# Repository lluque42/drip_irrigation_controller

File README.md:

# Drip irrigation controller

## Table of contents

- [Introduction](#introductions)
- [Building instructions](#building-instructions)
- [WiFi connectivity](#wifi-connectivity)
    - [UDP command messages](#udp-command-messages)
- [Directory tree](#directory-tree)
- [Hardware](#harware)

------

## Introduction

This drip irrigation controller was designed to control one relay for a water
electrovalve and a second relay for ornament lights. Both relays may be
configured for independent one-time-a-day activation to remain active during a
configurable time. The frequency in terms of days between activations is also
configurable. Any of the relays may be disabled which will stop their future scheduled activations.

A default configuration is applied at building time (edit files 'CMakeLists.txt',
'timers_default_data.cmake', and 'wlan_setup_data.cmake' to change it). The
controller configuration (get and set) and manual activation may be done
remotely through the wifi connection with simple UDP messages exchange.

This is the second controller I've built for my house plants.
The first was written in Python in a rush before going out on
a trip and worked perfectly. It had a dot matrix screen with
a setup menu through microswitches; a real-time clock module,
etc. But some years later it hangs a lot, outdoor installation
always takes its toll.

So I've decided to implement a new version that loses the screen
in favor of a WiFi connection for keep-alive signaling against
a server, configuration and commands.

This repository includes all the code and scripts to built the
program in a Raspberry Pi Pico (1) W board. The schematics for
the external hardware is also included.

**Luis Luque - 2025**

------

## Building instructions

REMEMBER: This code was made for and tested on a Pico W (first
family of the Raspberry Pi Pico series). Use at your own risk in
other platforms.

Clone repository from:

https://github.com/lluque42/drip_irrigation_controller.git

Two files are included to allow an easy customization:
* wlan_setup_data.cmake.template (rename to wlan_setup_data.cmake)
    * To enter the wifi SSID, password.
* timers_default_data.cmake
* To enter the time of the day, frequency and duration for
the relays activation.

Create a build directory and enter to it:

```bash
drip_irrigation_controller $ mkdir build
drip_irrigation_controller $ cd build
drip_irrigation_controller/build $
```

Once inside, execute cmake against the parent directory (where
the CMakeLists.txt is):

```bash
drip_irrigation_controller/build $ cmake ..
drip_irrigation_controller/build $
```

If no errors occurred, then a Makefile file should have been created
in the build directory. Execute it to build the binaries.

```bash
drip_irrigation_controller/build $ make
```

If everything ok, a number of binary files should've been produced,
among them a drip.elf or drip.uf2 ready to be loaded into the Pico W
board.

For building the tests tool, see the **Wifi connectivity** section.

If some error occur check the pre-requisites:
* The PICO_SDK_VARIABLE environment variable should exist and point to
the root of the pico-sdk directory.
* Is your board really a Pico W (first generation)?
* ?
TODO

------

## WiFi connectivity

The microcontroller can connect to a wireless network if the correct settings
were edited in the wlan_setup_data.cmake file (a template for this file is
provided, just write your settings and rename the file).

A static IPv4 address must be provided, as well as an UDP port (a high
non-common one to avoid issues). This is necessary for the controller to act as
a simple text UDP server. That is, it will open the UDP port listening for
incoming messages. A set of message formats define commands and responses
that may be sent to the controller and back.

The messages are plain-text ASCII, human readable, strings (without the NUL
termination), that is, a string sent as the payload of the UDP datagram.

A simple, dirty client (and a server) written to debug this program is included
as a git sub-module in:

```bash
drip_irrigation_controller/test/udp_tx_rx
```

Since it is a submodule it should be initialized from the
drip_irrigation_controller root directory by doing:

```bash
drip_irrigation_controller $ git submodule update --init --recursive
```

After that, both the client and server can be build with:

```bash
drip_irrigation_controller/test/udp_tx_rx $ make
```

Which places the binaries in the bin folder.

To use the client to communicate over the wifi with  the irrigation controller
(assuming the default values in the wlan_setup_data.cmake.template) just do:

```bash
.../test/udp_tx_rx/bin $ ./udp_client 192.168.1.69 1234
```

This will receive input from the stdin for the user to send text to the
controller.

The commands, their formats, and the expected replies are the following:

------

### UDP command messages

Below are the recognized command messages and their replies. The client
just need to write and read this as the payload of UDP messages to/from
the controller that acts as a server on the IP address and UDP port set
in the wlan_setup_data.cmake at build time.
* Set datetime:
	SET:DATETIME:YYYY:MM:DD:dotw:HH:mm:SS
		dotw: Day of the week 0-6. Sunday is 0.
* Set water timer parameters:
    SET:WATER:WTODHH:WTODmm:WTODSS:WEXD:DOW
        TOD: Time of day when activation should occur.
        EXD: Every X days, the X. Days between activations.
        DO:  Duration of activation.
* Set lights timer parameters:
    SET:LIGHTS:LTODHH:LTODmm:LTODSS:LEXD:DOL
        TOD: Time of day when activation should occur.
        EXD: Every X days, the X. Days between activations.
        DO:  Duration of activation.
* Get datetime:
    GET:DATETIME
        Response example: 2025:8:15:5:21:2:52
        (see SET:DATETIME format).
* Get water relay current configuration:
    GET:WATER
        Response example: 
            21:0:0:1:120:2025:8:15:5:21:0:0
        That is:
            Time of day: 21:0:0
            Every X days: 1
            Duration (sec): 120
            Next activation scheduled: 2025:8:16:6:21:0:0
            (see SET:DATETIME format).
* Get lights relay current configuration:
    GET:LIGHTS 
        Response example:
            21:0:0:1:10800:2025:8:15:5:21:0:0
        See GET:WATER format.
* Manual on lights.
	MANUALON:LIGHTS
* Manual off lights.
	MANUALOFF:LIGHTS
* Manual on water.
	MANUALON:WATER
* Manual off water.
	MANUALOFF:WATER
* Timed on lights (Force turn on for the duration configured).
	TIMEDON:LIGHTS
* Timed on irigation (Force turn on for the duration configured).
	TIMEDON:WATER

For non get commands, expect a response of "done" if it was correctly processed
or a custom human readable error message.

------

## Directory tree

TODO

    ./  
    ├── .gitignore				(to prevent undesired files to be stagged)
    ├── Doxyfile				(doxygen config file for doc generation)  
    ├── Makefile				(use 'make help' for instructions)  
    ├── README.md				(brief documentation)  
    ├── doc/					(documentation extracted from comments in .h)  
    │   ├── html/				(html documentation)  
    │   │   ├── ...  
    │   │   ├── index.html		(entry point for html documentation)  
    │   │   ├── ...  
    │   └── man/				(man pages documentation)  
    │       └── man3/  
    │           └── ...			(example of use: 'man -l ft_string.h.3')  
    ├── include/				(directory for public header files (.h))  
    │   ├── ...  
    │   └── ...  
    ├── src/					(dir for source code and private header files)  
    │   ├── ...  
    │   │   ├── ...  				
    │   │   └── ...  
    │   └── ...					(may be structured in several directories)  
    │       ├── ...  
    │       └── ...  
    ├── lib/					(external libraries)  
    │   ├── ...  
    │   └── libft				(each library in its own directory)  
    ├── bin/					(directory for project's binaries and tester)  
    │   ├── ...  
    │   └── ...					(may be structured in several directories)  
    ├── obj/					(dir for source code and private header files)  
    │   ├── ...  
    │   │   ├── ...  
    │   │   └── ...  
    │   └── ...					(structured as in ./src)  
    │       ├── ...  
    │       └── ...  
    ├── data/					(directory for non-source files)  
    └── test/					(test program src code, compiles to .bin/tester)
        ├── ...  
        ├── tester.c  
        └── ...  

------

## Hardware

TODO

Volts across led: 2,5 V 
	With a 10K resistance and driven through the 2n3904 (100KOhm base to gpio)

With USB 5V directly fed, the relay coil consumes 70mA
	The pico restarts everytime te coil de-energizes, the diode requirement is
	real.

Had to replace the 100K base resistor with a 10K because with the realy coil
current I guess the transistor couldn't remain polarized.

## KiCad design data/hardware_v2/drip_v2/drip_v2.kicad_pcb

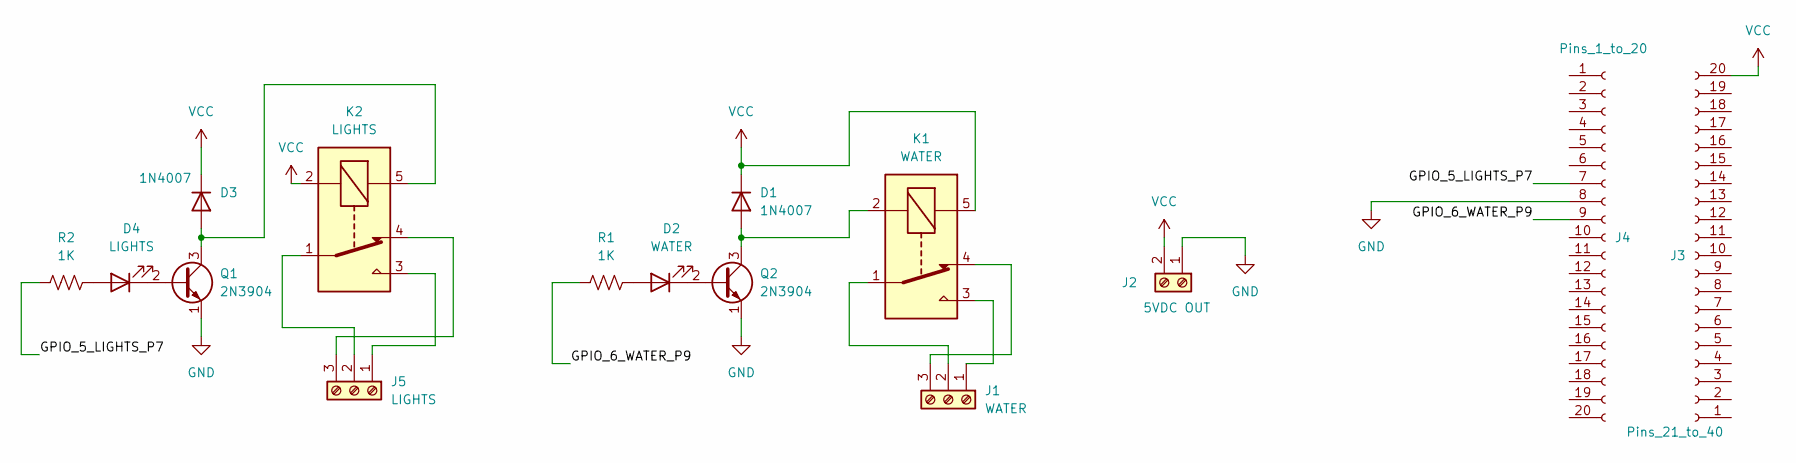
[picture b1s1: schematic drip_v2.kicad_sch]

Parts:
D1, D3: 1N4007; D_DO-41_SOD81_P10.16mm_Horizontal
D2: WATER; LED_D3.0mm
D4: LIGHTS; LED_D3.0mm
J1: WATER; TerminalBlock_Phoenix_MKDS-1,5-3_1x03_P5.00mm_Horizontal
J2: 5VDC OUT; TerminalBlock_Phoenix_MKDS-1,5-2_1x02_P5.00mm_Horizontal
J3: Pins_21_to_40; PinSocket_1x20_P2.54mm_Vertical
J4: Pins_1_to_20; PinSocket_1x20_P2.54mm_Vertical
J5: LIGHTS; TerminalBlock_Phoenix_MKDS-1,5-3_1x03_P5.00mm_Horizontal
K1: WATER; Relay_SPDT_SANYOU_SRD_Series_Form_C
K2: LIGHTS; Relay_SPDT_SANYOU_SRD_Series_Form_C
Q1, Q2: 2N3904; TO-92_Inline
R1, R2: 1K; R_Axial_DIN0207_L6.3mm_D2.5mm_P7.62mm_Horizontal

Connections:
/GPIO_5_LIGHTS_P7: J4.7, R2.1
/GPIO_6_WATER_P9: J4.9, R1.1
GND: J2.1, J4.8, Q1.1 (E), Q2.1 (E)
unnamed: D1.2 (A), K1.2, Q2.3 (C)
unnamed: D2.2 (A), R1.2
unnamed: D2.1 (K), Q2.2 (B)
unnamed: D3.2 (A), K2.5, Q1.3 (C)
unnamed: D4.2 (A), R2.2
unnamed: D4.1 (K), Q1.2 (B)
unnamed: J1.1, K1.3
unnamed: J1.2, K1.1
unnamed: J1.3, K1.4
unnamed: J5.1, K2.3
unnamed: J5.2, K2.1
unnamed: J5.3, K2.4
VCC: D1.1 (K), D3.1 (K), J2.2, J3.20, K1.5, K2.2

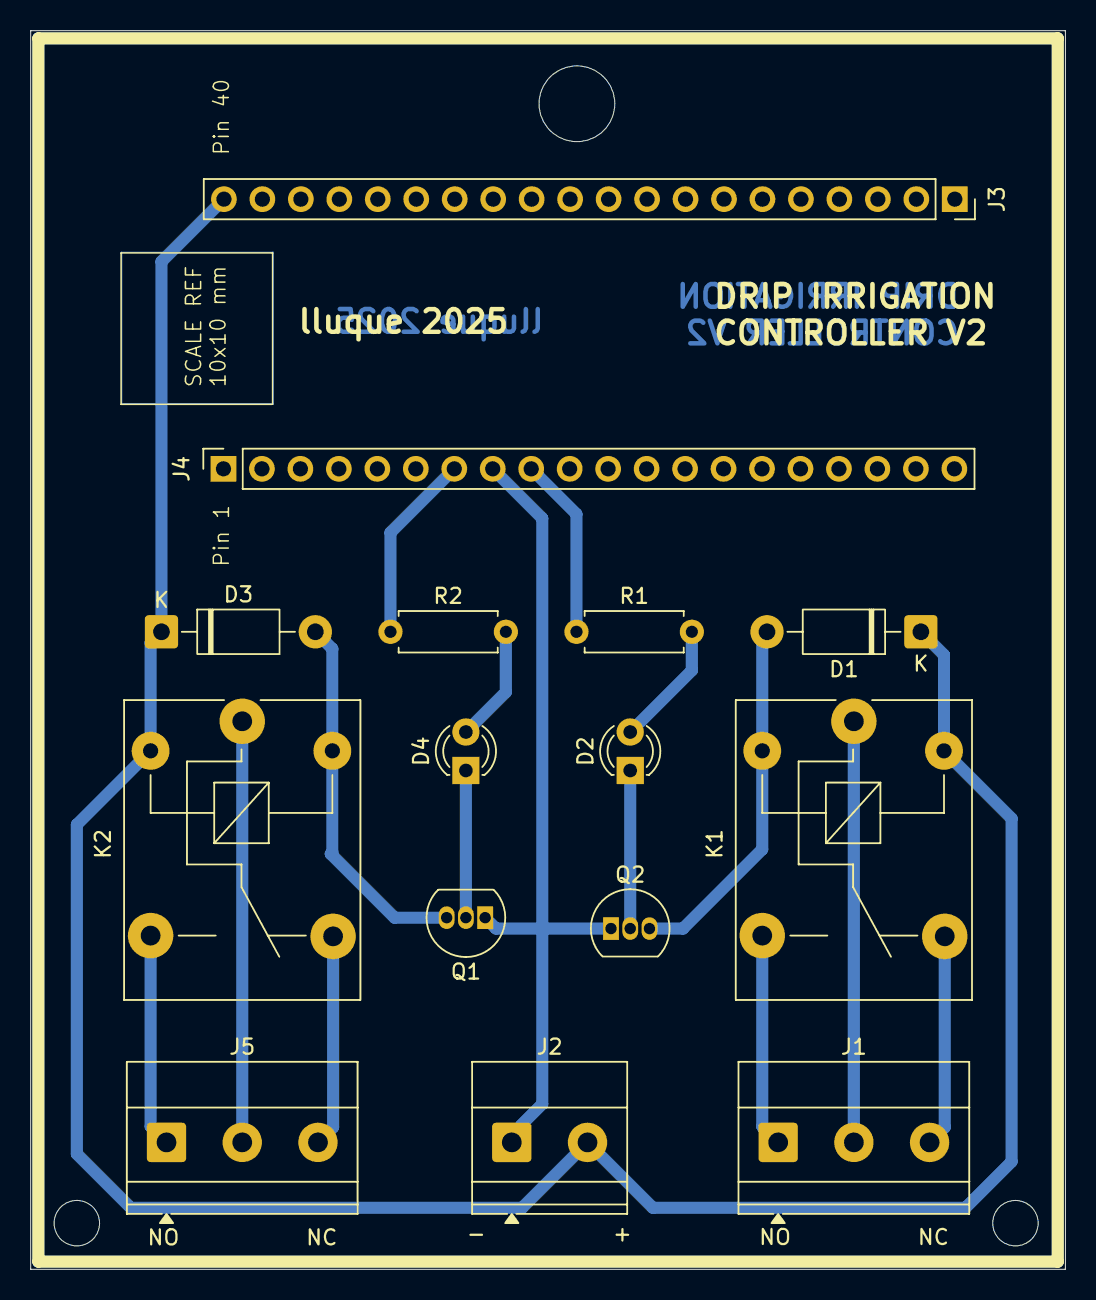
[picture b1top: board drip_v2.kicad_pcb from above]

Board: 2 copper layers, 68.3 x 81.8 mm, 15 parts (0 on the bottom side), 16 nets.

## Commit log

2025-08-07 ADDed preliminary README.md and TODO doc template
    First commit on main. Now moving to development branch...
2025-08-07 ADD gitignore and basic building capabilities
    A heavily commented template for CMakeLists.txt was added from
    scratch to test and document my knowledge. The "pico_sdk_import.cmake"
    was copied from the SDK directory. A dummy main.c was added. It
    builds with no problem.
    In the CMakeLists.txt I tried a couple of strategies to build
    with no additional arguments (board type, wlan connection data) and
2025-08-08 ADD USB capabilities for debugging
    With not much effort our project links now with the USB component
    allowing a USB serial communication for debugging (/dev/ttyACM0).
2025-08-09 ADD RTC and alarm capabilities, on-board LED
    The setting and getting of date time using the RP-2040 internal RTC
    was tested succesfully. Also the alarm feature in terms of absolute
    time (when a particular value of any of the non-minus-one time fields
    match with the current time) was tested using a callback function of
    mine.
    The on-board LED control was also tested. The board is a Pico W so
2025-08-09 ADDed a native gpio as output
    Of course it works...
2025-08-11 ADDed WiFi capabilities and static ip address
    More proof-of-concepts achieved regarding the network capabilities.
    I had to deep into the lwIP own documentation and source code to
    understand a couple of things and get the desired results.
    The generic lwipopts.h was added.
    Also a document for some comments on the hardware.
    By the way, in the real world and against all odds, I manage to
2025-08-11 REFACTORIZATION The first serious clean up
    A more organized tree directory was built. Functions were taken
    out the main.c, renamed with a prefix to show their functionality
    area, and put into their own files.
    A template for the WiFi configuration was added with useful comments
    for a straight forward customization: wlan_setup_data.cmake.template.
    In a similar fashion, another file was added with the default timers
2025-08-13 ADDed more network capabilities: UDP server
    The UDP server that receives and echoes bytes is working.
    When a NUL terminated c-string "1" is received, the water relay
    coil is energized, with "3" it's turned off. The same for the
    lights relay with "2" (ON) and "4" (OFF).
    The authentication type was added to the
    wlan_setup_data.cmake.template using the macros defined by cyw43:
2025-08-14 ADDed loading of default settings from build data
    Improved drip_rtc_str2datetime() with more fool-proof error checking.
    Added a struct type for the timers setting values and a function to
    load them from the buildtime macro values on timers_default_data.cmake.
    The default settings from CMake macros are now loaded into the program.
2025-08-15 ADD Scheduled relay activaton for required durations
    Activation and de-activation of relays by chaining alarm scheduling
    was added. The API used was the pico_time alarm pool that uses
    absolute time (usec since boot) so utils functions for time
    conversion amd manipulation were added (e.g. human-readable
    datetime_t struct to usec epoch; uint64 usec relative time offset
    of the absolute time to the usec epoc RTC at the time of setting)
2025-08-16 ADDed remote control & config WiFi-UDP
    Implemented the "every 0 days" option meaning do-not-schedule.
    Added more strict compilation flags and fixed every pending warning.
    A description and the repo url were added as binary metadata.
    Added a generic mechanism (beyond loading and applying the default
    settings) to allow the enforcement of new settings during runtime:
    cancel scheduled alarms, re-compute the RTC time offset,
2025-08-17 ADDed images of hardware to README.md
    The README.md was improved and actual images of the controller
    were added.
2025-10-15 FIX wifi unresponsive after a day
    The lwiopts.h was modified to disable the DHCP. The static
    address is configured before connecting to the WLAN. This
    proved to be the solution for the freezing of the wifi
    connection after some time working fine.
    Some refactorization was made.
2025-11-12 New hardware
    A new PCB was designed to replace the old one that got wet.
    The outputs were moved to new GPIOs.
